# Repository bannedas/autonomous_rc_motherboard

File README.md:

# Autonomous RC motherboard

Remake of Benjamin Vedder made project https://github.com/vedderb/rise_sdvp

## Main

```
- Raspberry Compute module 3
	- HDMI
	- CAM0
	- ETHERNET
	- USB HOST (4 USB OUT)
	- microSD
- DAS board
- 2.4GHz radio by CC2520 
	- CC2592 extender
	- External antenna
- 420MHz - 470MHz radio by CC120
	- External antenna
-RTK-GNSS
	- UBLOX NEO M8P module
	- External antenna

- 40V to 12V 3A power
- 12V to 5V 1A power
- 12V to 3V3 2A power
- 3V3 to 1V8 500mA power

- 2x CAN output
- 4x PWM output
- 1 uart output

- Status LED for everything

```

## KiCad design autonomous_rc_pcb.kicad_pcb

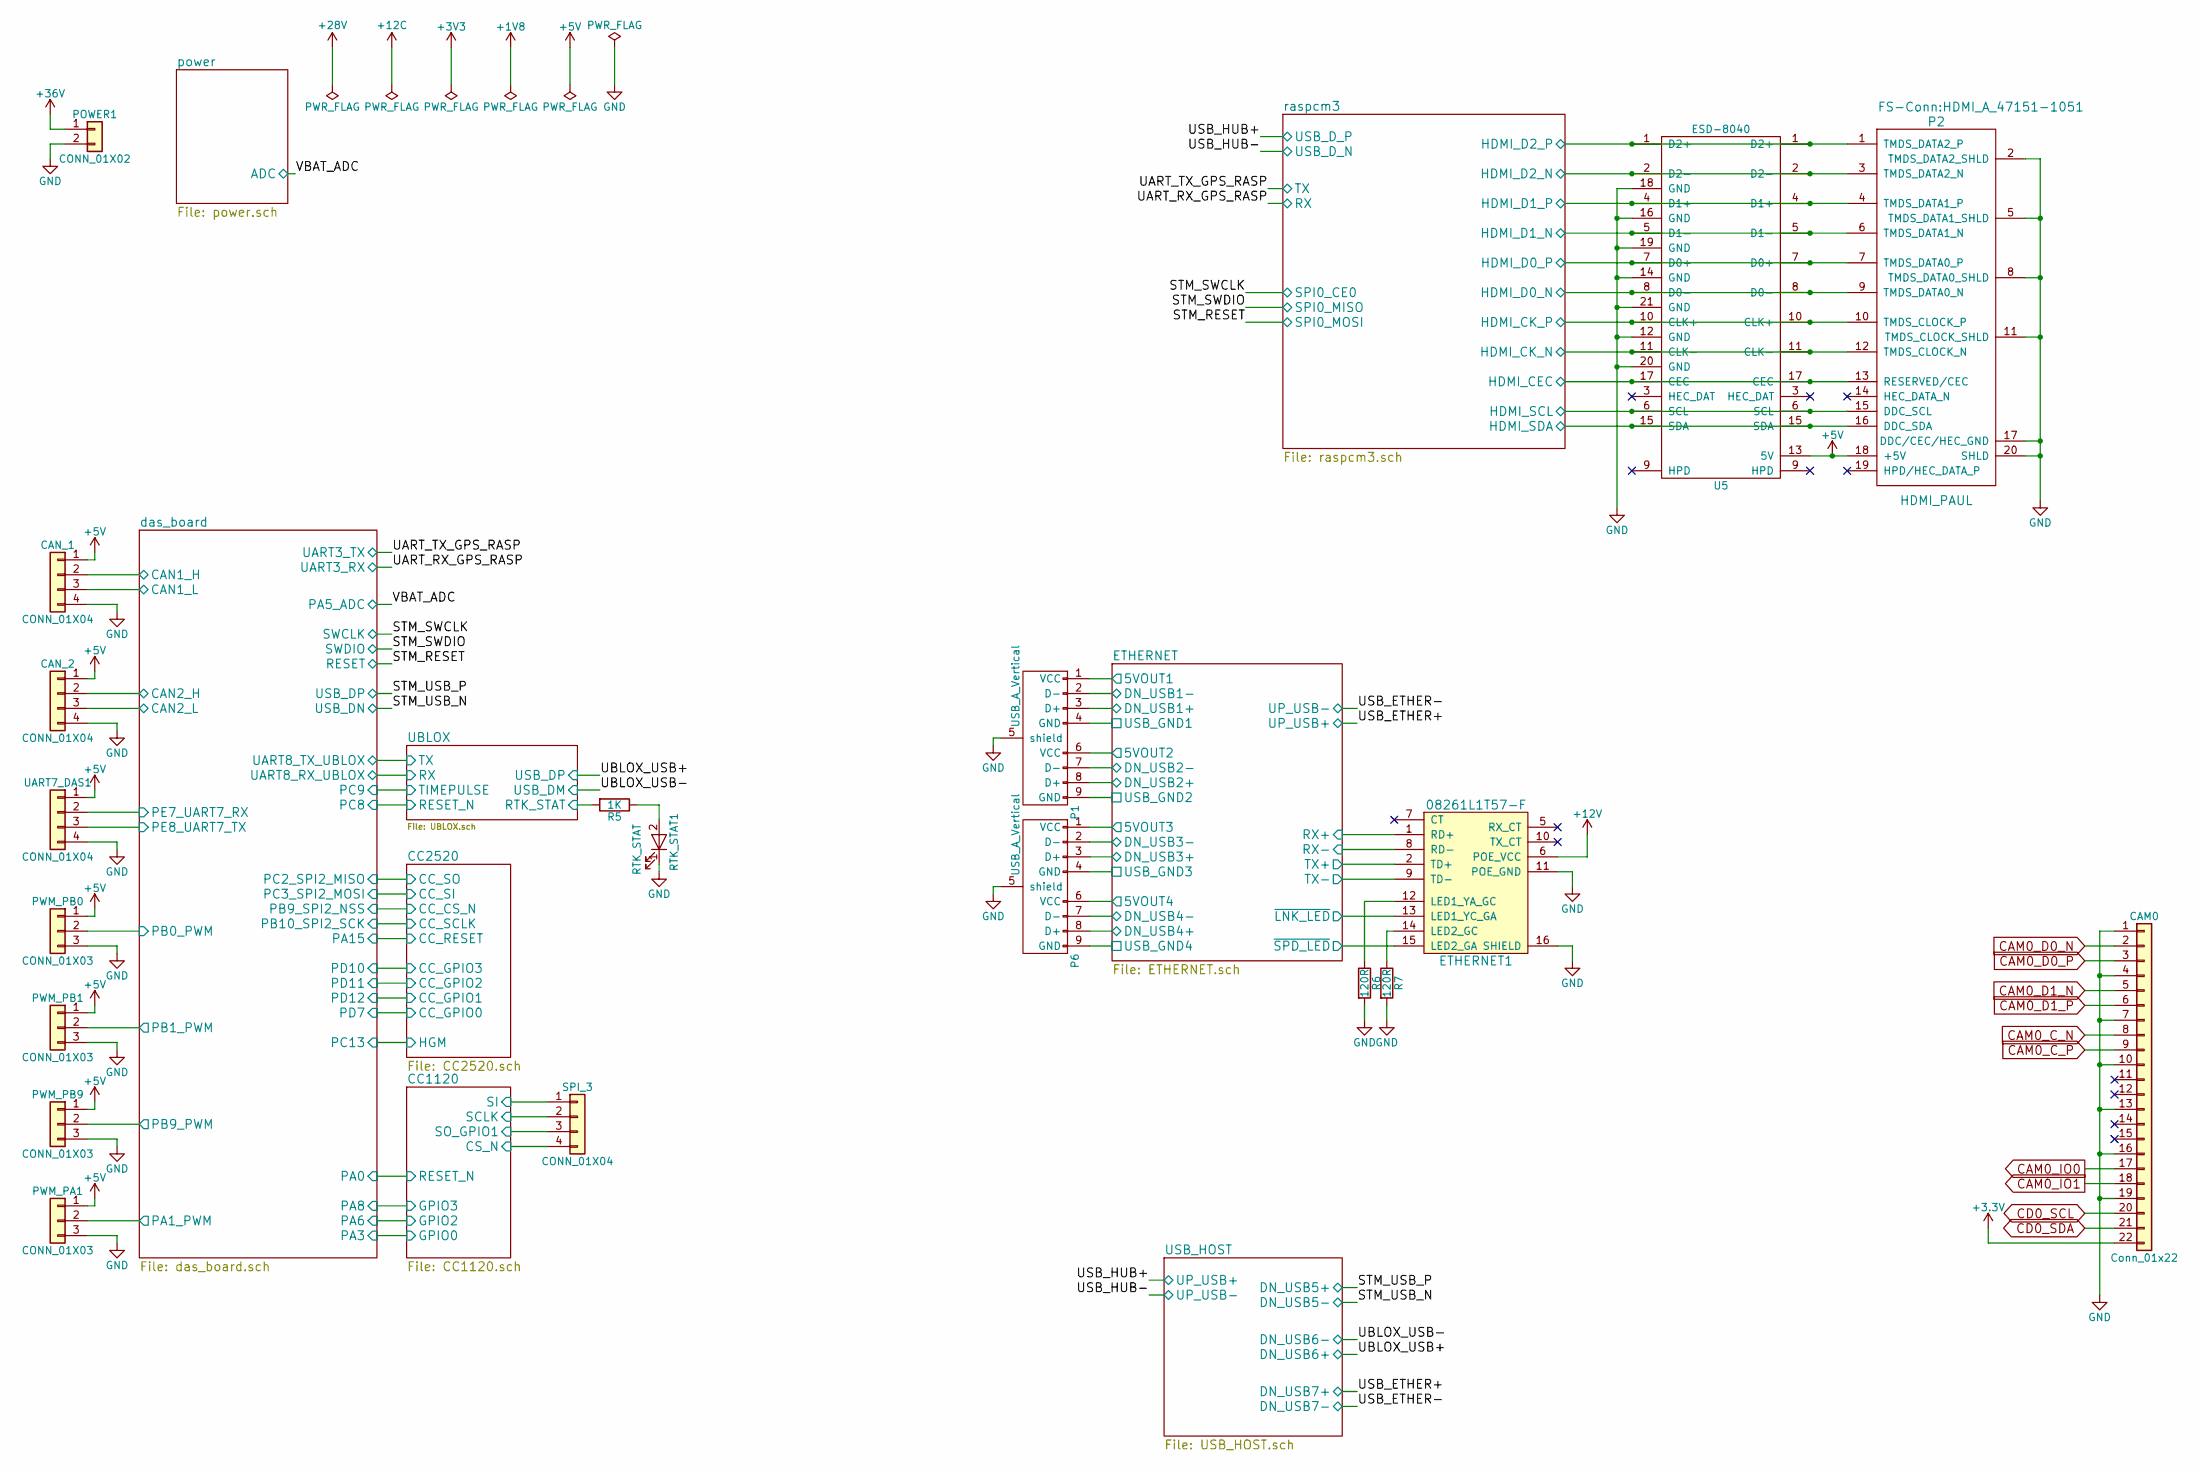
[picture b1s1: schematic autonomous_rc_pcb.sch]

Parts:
CAM0: Conn_01x22; 54548-2271; MPN 54548-2271
CAN_1, CAN_2: CONN_01X04; Molex_PicoBlade_53261-0471_04x1.25mm_Angled
ETHERNET1: 08261L1T57-F; 0826-1L1T-57-F; MPN 08261L1T57-F
P1, P6: USB_A_Vertical; USB-A-vertical
P2: HDMI_PAUL; HDMI_A_47151-1051
POWER1: CONN_01X02; DuraClik2
PWM_PA1: CONN_01X03; Molex_PicoBlade_53261-0371_03x1.25mm_Angled
PWM_PB0, PWM_PB1, PWM_PB9: CONN_01X03; Molex_PicoBlade_53261-0371_03x1.25mm_Angled
R5: 1K; R_0402
R6, R7: 120R; R_0402
RTK_STAT1: RTK_STAT; LED_0603
SPI_3: CONN_01X04; Molex_PicoBlade_53398-0471_04x1.25mm_Straight
U5: ESD-8040; ESD8040
UART7_DAS1: CONN_01X04; Molex_PicoBlade_53261-0471_04x1.25mm_Angled

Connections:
+5V: CAN_1.1, CAN_2.1, P2.18 (+5V), PWM_PA1.1, PWM_PB0.1, PWM_PB1.1, PWM_PB9.1, U5.13 (5V), UART7_DAS1.1; also elsewhere on the board
+12V: ETHERNET1.6 (POE_VCC); also elsewhere on the board
+36V: POWER1.1; also elsewhere on the board
/CC1120/CS_N: SPI_3.4; also elsewhere on the board
/CC1120/SCLK: SPI_3.2; also elsewhere on the board
/CC1120/SI: SPI_3.1; also elsewhere on the board
/CC1120/SO_GPIO1: SPI_3.3; also elsewhere on the board
/ETHERNET/5VOUT3: P1.1 (VCC); also elsewhere on the board
/ETHERNET/5VOUT4: P1.6 (VCC); also elsewhere on the board
/ETHERNET/DN_USB3+: P1.3 (D+); also elsewhere on the board
/ETHERNET/DN_USB3-: P1.2 (D-); also elsewhere on the board
/ETHERNET/DN_USB4+: P1.8 (D+); also elsewhere on the board
/ETHERNET/DN_USB4-: P1.7 (D-); also elsewhere on the board
/ETHERNET/RX+: ETHERNET1.1 (RD+); also elsewhere on the board
/ETHERNET/RX-: ETHERNET1.8 (RD-); also elsewhere on the board
/ETHERNET/TX+: ETHERNET1.2 (TD+); also elsewhere on the board
/ETHERNET/TX-: ETHERNET1.9 (TD-); also elsewhere on the board
/ETHERNET/USB_GND3: P1.4 (GND); also elsewhere on the board
/ETHERNET/USB_GND4: P1.9 (GND); also elsewhere on the board
/ETHERNET/~LNK_LED: ETHERNET1.13 (LED1_YC_GA); also elsewhere on the board
/ETHERNET/~SPD_LED: ETHERNET1.15 (LED2_GA); also elsewhere on the board
/UBLOX/RTK_STAT: R5.2; also elsewhere on the board
/das_board/CAN1_H: CAN_1.2; also elsewhere on the board
/das_board/CAN1_L: CAN_1.3; also elsewhere on the board
/das_board/CAN2_H: CAN_2.2; also elsewhere on the board
/das_board/CAN2_L: CAN_2.3; also elsewhere on the board
/das_board/PA1_PWM: PWM_PA1.2; also elsewhere on the board
/das_board/PB0_PWM: PWM_PB0.2; also elsewhere on the board
/das_board/PB1_PWM: PWM_PB1.2; also elsewhere on the board
/das_board/PB9_PWM: PWM_PB9.2; also elsewhere on the board
/das_board/PE7_UART7_RX: UART7_DAS1.2; also elsewhere on the board
/das_board/PE8_UART7_TX: UART7_DAS1.3; also elsewhere on the board
/raspcm3/HDMI_CEC: P2.13 (RESERVED/CEC), U5.17 (CEC); also elsewhere on the board
/raspcm3/HDMI_CK_N: P2.12 (TMDS_CLOCK_N), U5.11 (CLK-); also elsewhere on the board
/raspcm3/HDMI_CK_P: P2.10 (TMDS_CLOCK_P), U5.10 (CLK+); also elsewhere on the board
/raspcm3/HDMI_D0_N: P2.9 (TMDS_DATA0_N), U5.8 (D0-); also elsewhere on the board
/raspcm3/HDMI_D0_P: P2.7 (TMDS_DATA0_P), U5.7 (D0+); also elsewhere on the board
/raspcm3/HDMI_D1_N: P2.6 (TMDS_DATA1_N), U5.5 (D1-); also elsewhere on the board
/raspcm3/HDMI_D1_P: P2.4 (TMDS_DATA1_P), U5.4 (D1+); also elsewhere on the board
/raspcm3/HDMI_D2_N: P2.3 (TMDS_DATA2_N), U5.2 (D2-); also elsewhere on the board
/raspcm3/HDMI_D2_P: P2.1 (TMDS_DATA2_P), U5.1 (D2+); also elsewhere on the board
/raspcm3/HDMI_SCL: P2.15 (DDC_SCL), U5.6 (SCL); also elsewhere on the board
/raspcm3/HDMI_SDA: P2.16 (DDC_SDA), U5.15 (SDA); also elsewhere on the board
CAM0_C_N: CAM0.8; also elsewhere on the board
CAM0_C_P: CAM0.9; also elsewhere on the board
CAM0_D0_N: CAM0.2; also elsewhere on the board
CAM0_D0_P: CAM0.3; also elsewhere on the board
CAM0_D1_N: CAM0.5; also elsewhere on the board
CAM0_D1_P: CAM0.6; also elsewhere on the board
CAM0_IO0: CAM0.17; also elsewhere on the board
CAM0_IO1: CAM0.18; also elsewhere on the board
CD0_SCL: CAM0.20; also elsewhere on the board
CD0_SDA: CAM0.21; also elsewhere on the board
GND: CAM0.1, CAM0.4, CAM0.7, CAM0.10, CAM0.13, CAM0.16, CAM0.19, CAN_1.4, CAN_2.4, ETHERNET1.11 (POE_GND), ETHERNET1.16 (SHIELD), P1.5 (shield), P2.2 (TMDS_DATA2_SHLD), P2.5 (TMDS_DATA1_SHLD), P2.8 (TMDS_DATA0_SHLD), P2.11 (TMDS_CLOCK_SHLD), P2.17 (DDC/CEC/HEC_GND), P2.20 (SHLD), P6.5 (shield), POWER1.2, PWM_PA1.3, PWM_PB0.3, PWM_PB1.3, PWM_PB9.3, R6.2, R7.2, RTK_STAT1.1 (K), U5.12 (GND), U5.14 (GND), U5.16 (GND), U5.18 (GND), U5.19 (GND), U5.20 (GND), U5.21 (GND), UART7_DAS1.4; also elsewhere on the board
unnamed 253: R5.1, RTK_STAT1.2 (A); also elsewhere on the board
unnamed: ETHERNET1.12 (LED1_YA_GC), R6.1
unnamed: ETHERNET1.14 (LED2_GC), R7.1

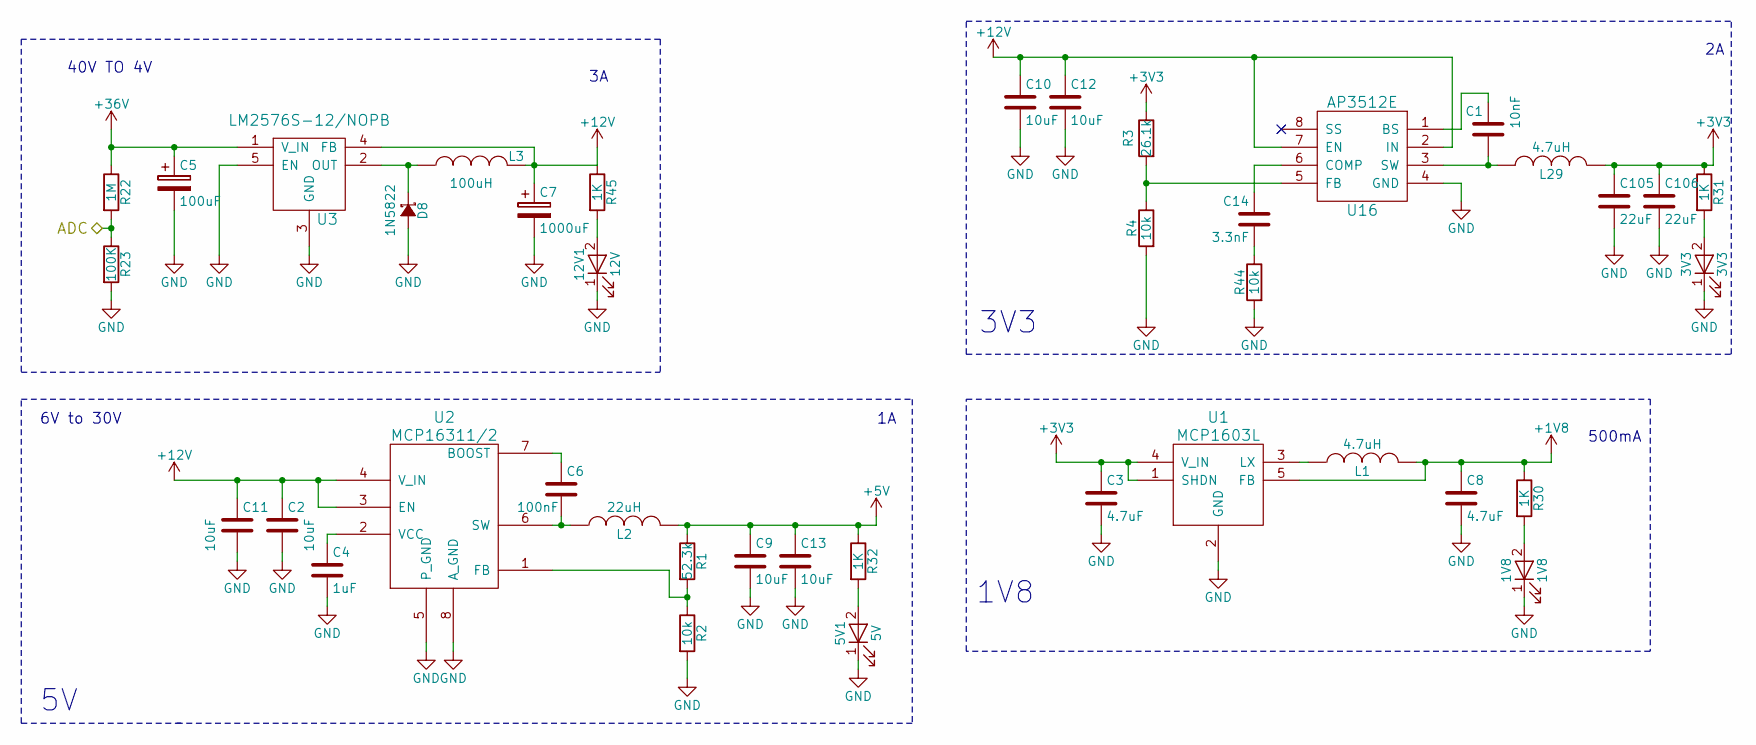
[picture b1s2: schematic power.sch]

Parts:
1V8: 1V8; LED_0603
3V3: 3V3; LED_0603
5V1: 5V; LED_0603
12V1: 12V; LED_0603
C1: 10nF; C_0402
C2, C9, C11, C13: 10uF; C_0402
C3, C8: 4.7uF; C_0402
C4: 1uF; C_0402
C5: 100uF; CP_Radial_D8.0mm_P3.50mm
C6: 100nF; C_0402
C7: 1000uF; CP_Radial_D8.0mm_P5.00mm; MPN EEUFR1C102LB
C10, C12: 10uF; C_0805_HandSoldering
C14: 3.3nF; C_0402
C105, C106: 22uF; C_0805_HandSoldering
D8: 1N5822; D_DO-201AD_P5.08mm_Vertical_AnodeUp
L1: 4.7uH; R_0805_HandSoldering; MPN CPI0805E4R7R-10
L2: 22uH; L_Coilcraft_XAL5030; MPN VLCF5020T-220MR75-1
L3: 100uH; L_Vishay_IHLP-4040; MPN MSS1210-104KED
L29: 4.7uH; L_Taiyo-Yuden_NR-50xx_HandSoldering; MPN SRN4018-4R7M
R1: 52.3k; R_0402
R2: 10k; R_0402
R3: 26.1k; R_0402_1005Metric
R4, R44: 10k; R_0402_1005Metric
R22: 1M; R_0402
R23: 100K; R_0402
R30, R31, R32, R45: 1K; R_0402
U1: MCP1603L; TSOT-23-5; MPN MCP1603LT-180I/OS
U2: MCP16311/2; MSOP-8-1EP_3x3mm_Pitch0.65mm
U3: LM2576S-12/NOPB; TO-263-5_TabPin3; MPN LM2576S-12/NOPB
U16: AP3512E; PowerIntegrations_SO-8

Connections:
+1V8: C8.1, L1.2, R30.1, U1.5 (FB); also elsewhere on the board
+5V: C9.1, C13.1, L2.2, R1.1, R32.1; also elsewhere on the board
+12V: C2.1, C7.1, C10.1, C11.1, C12.1, L3.2, R45.1, U2.3 (EN), U2.4 (V_IN), U3.4 (FB), U16.2 (IN), U16.7 (EN); also elsewhere on the board
+36V: C5.1, R22.1, U3.1 (V_IN); also elsewhere on the board
/VBAT_ADC: R22.2, R23.1; also elsewhere on the board
GND: 1V8.1 (K), 3V3.1 (K), 5V1.1 (K), 12V1.1 (K), C2.2, C3.2, C4.2, C5.2, C7.2, C8.2, C9.2, C10.2, C11.2, C12.2, C13.2, C105.2, C106.2, D8.A, R2.2, R4.2, R23.2, R44.2, U1.2 (GND), U2.5 (P_GND), U2.8 (A_GND), U3.3 (GND), U3.5 (EN), U16.4 (GND); also elsewhere on the board
unnamed: 12V1.2 (A), R45.2
unnamed: C1.1, U16.1 (BS)
unnamed: C1.2, L29.2, U16.3 (SW)
unnamed: C4.1, U2.2 (VCC)
unnamed: C6.1, U2.7 (BOOST)
unnamed: C6.2, L2.1, U2.6 (SW)
unnamed: C14.1, U16.6 (COMP)
unnamed: C14.2, R44.1
unnamed: 1V8.2 (A), R30.2
unnamed: 3V3.2 (A), R31.2
unnamed 259: 5V1.2 (A), R32.2; also elsewhere on the board
unnamed: D8.K, L3.1, U3.2 (OUT)
unnamed: L1.1, U1.3 (LX)
unnamed: R1.2, R2.1, U2.1 (FB)
unnamed: R3.2, R4.1, U16.5 (FB)

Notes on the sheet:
6V to 30V
1V8
3V3
500mA
40V TO 4V

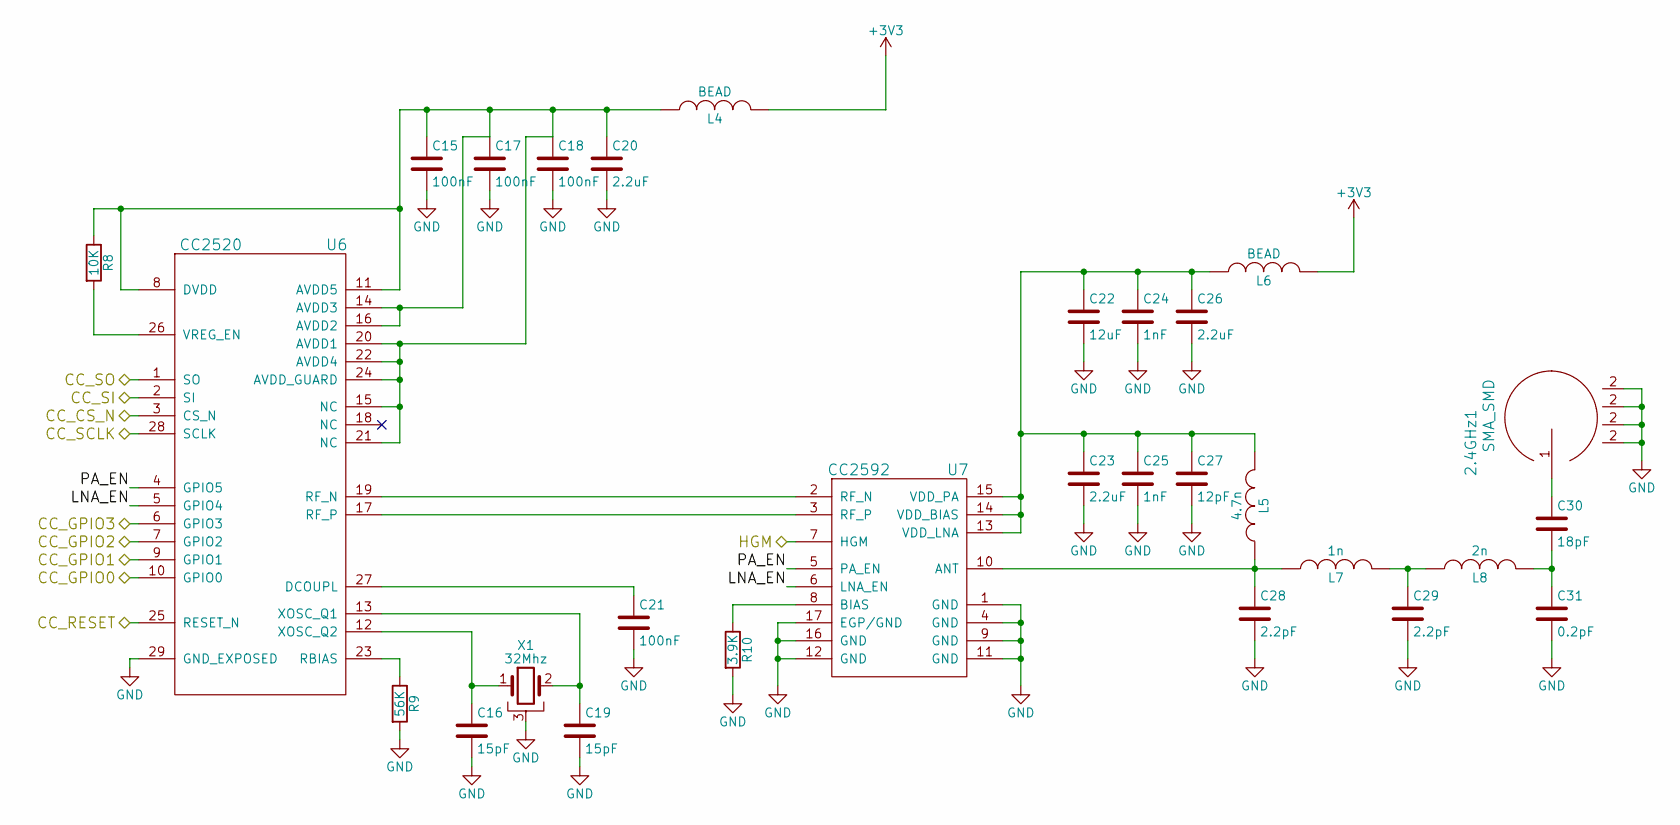
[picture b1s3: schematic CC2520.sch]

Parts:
2.4GHz1: SMA_SMD; SMA_THT_Jack_Straight
C15, C17, C18, C21: 100nF; C_0402
C16, C19: 15pF; C_0603
C20, C23, C26: 2.2uF; C_0603_1608Metric
C22: 12uF; C_1210_3225Metric
C24, C25: 1nF; C_0402
C27: 12pF; C_1210_3225Metric
C28, C29: 2.2pF; C_0603_1608Metric
C30: 18pF; C_0402
C31: 0.2pF; C_0402
L4, L6: BEAD; R_0603; MPN BLM18HE152SN1
L5: 4.7n; R_0402
L7: 1n; R_0402
L8: 2n; R_0402
R8: 10K; R_0402
R9: 56K; R_0402
R10: 3.9K; R_0402
U6: CC2520; QFN-28-1EP_5x5mm_Pitch0.5mm; MPN CC2520RHDR
U7: CC2592; QFN-16-1EP_4x4mm_Pitch0.65mm; MPN CC2592RGVR
X1: 32Mhz; Crystal_SMD_5032-4pin_5.0x3.2mm

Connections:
/CC2520/CC_CS_N: U6.3 (CS_N); also elsewhere on the board
/CC2520/CC_GPIO0: U6.10 (GPIO0); also elsewhere on the board
/CC2520/CC_GPIO1: U6.9 (GPIO1); also elsewhere on the board
/CC2520/CC_GPIO2: U6.7 (GPIO2); also elsewhere on the board
/CC2520/CC_GPIO3: U6.6 (GPIO3); also elsewhere on the board
/CC2520/CC_RESET: U6.25 (RESET_N); also elsewhere on the board
/CC2520/CC_SCLK: U6.28 (SCLK); also elsewhere on the board
/CC2520/CC_SI: U6.2 (SI); also elsewhere on the board
/CC2520/CC_SO: U6.1 (SO); also elsewhere on the board
/CC2520/HGM: U7.7 (HGM); also elsewhere on the board
/CC2520/LNA_EN: U6.5 (GPIO4), U7.6 (LNA_EN)
/CC2520/PA_EN: U6.4 (GPIO5), U7.5 (PA_EN)
GND: 2.4GHz1.2, C15.2, C16.2, C17.2, C18.2, C19.2, C20.2, C21.2, C22.2, C23.2, C24.2, C25.2, C26.2, C27.2, C28.2, C29.2, C31.2, R9.2, R10.2, U6.29 (GND_EXPOSED), U7.1 (GND), U7.4 (GND), U7.9 (GND), U7.11 (GND), U7.12 (GND), U7.16 (GND), U7.17 (EGP/GND), X1.3; also elsewhere on the board
unnamed: C15.1, C17.1, C18.1, C20.1, L4.1, R8.1, U6.8 (DVDD), U6.11 (AVDD5), U6.14 (AVDD3), U6.15 (NC), U6.16 (AVDD2), U6.20 (AVDD1), U6.21 (NC), U6.22 (AVDD4), U6.24 (AVDD_GUARD)
unnamed: C16.1, U6.12 (XOSC_Q2), X1.1
unnamed: C19.1, U6.13 (XOSC_Q1), X1.2
unnamed: C21.1, U6.27 (DCOUPL)
unnamed: C22.1, C23.1, C24.1, C25.1, C26.1, C27.1, L5.2, L6.1, U7.13 (VDD_LNA), U7.14 (VDD_BIAS), U7.15 (VDD_PA)
unnamed 216: C28.1, L5.1, L7.1, U7.10 (ANT); also elsewhere on the board
unnamed: C29.1, L7.2, L8.1
unnamed 218: 2.4GHz1.1, C30.1; also elsewhere on the board
unnamed: C30.2, C31.1, L8.2
unnamed: R8.2, U6.26 (VREG_EN)
unnamed: R9.1, U6.23 (RBIAS)
unnamed: R10.1, U7.8 (BIAS)
unnamed: U6.17 (RF_P), U7.3 (RF_P)
unnamed: U6.19 (RF_N), U7.2 (RF_N)

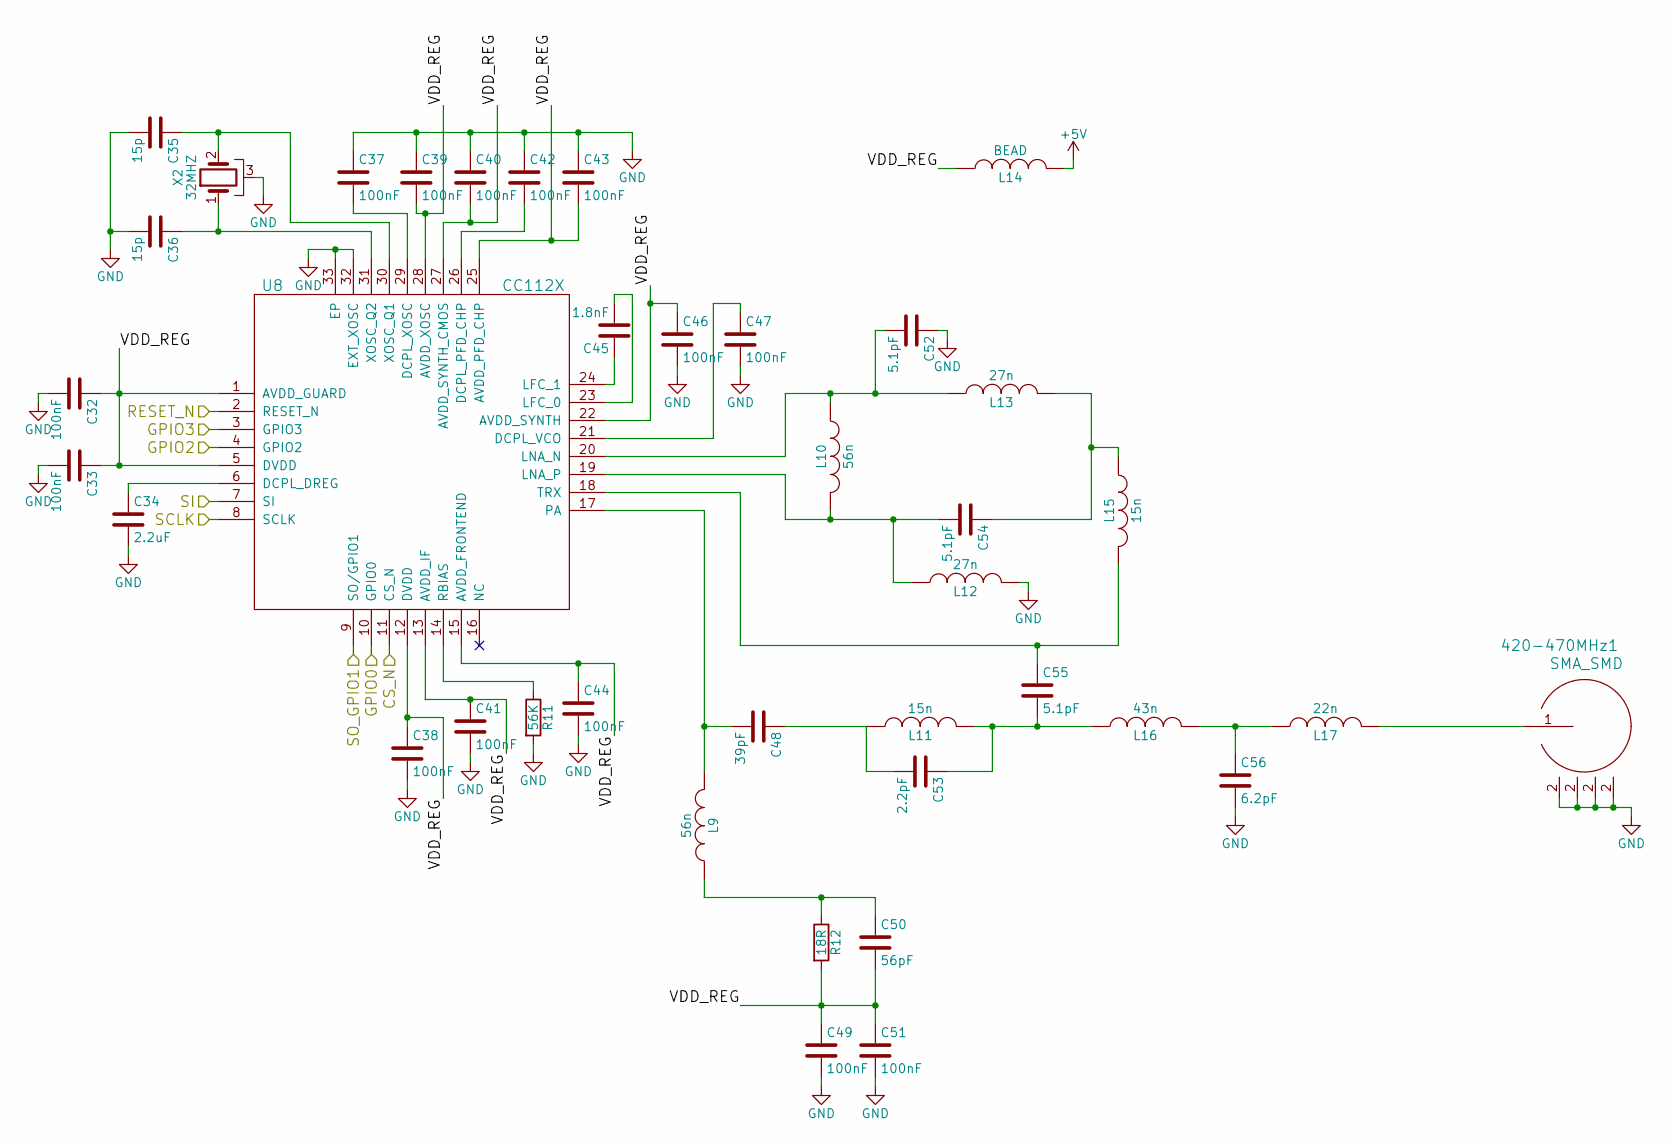
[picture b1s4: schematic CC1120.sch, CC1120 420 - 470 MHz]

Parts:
420-470MHz1: SMA_SMD; SMA_THT_Jack_Straight
C32, C33, C37, C38, C39, C40, C41, C42, C43, C44, C46, C47, C49, C51: 100nF; C_0402
C34: 2.2uF; C_0603
C35, C36: 15p; C_0603
C45: 1.8nF; C_0402
C48: 39pF; C_0402
C50: 56pF; C_0402
C52, C54, C55: 5.1pF; C_0402
C53: 2.2pF; C_0402
C56: 6.2pF; C_0402
L9, L10: 56n; R_0402
L11, L15: 15n; R_0402
L12, L13: 27n; R_0402
L14: BEAD; R_0603; MPN BLM18HE152SN1
L16: 43n; R_0402
L17: 22n; R_0402
R11: 56K; R_0402
R12: 18R; R_0402
U8: CC112X; QFN-32-1EP_5x5mm_Pitch0.5mm
X2: 32MHZ; Crystal_SMD_5032-4pin_5.0x3.2mm

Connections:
+5V: L14.2; also elsewhere on the board
/CC1120/CS_N: U8.11 (CS_N); also elsewhere on the board
/CC1120/GPIO0: U8.10 (GPIO0); also elsewhere on the board
/CC1120/GPIO2: U8.4 (GPIO2); also elsewhere on the board
/CC1120/GPIO3: U8.3 (GPIO3); also elsewhere on the board
/CC1120/SCLK: U8.8 (SCLK); also elsewhere on the board
/CC1120/SI: U8.7 (SI); also elsewhere on the board
/CC1120/SO_GPIO1: U8.9 (SO/GPIO1); also elsewhere on the board
/CC1120/VDD_REG: C32.1, C33.1, C38.1, C39.2, C40.2, C41.1, C43.2, C44.1, C46.1, C49.1, C50.2, C51.1, L14.1, R12.2, U8.1 (AVDD_GUARD), U8.5 (DVDD), U8.12 (DVDD), U8.13 (AVDD_IF), U8.15 (AVDD_FRONTEND), U8.22 (AVDD_SYNTH), U8.25 (AVDD_PFD_CHP), U8.27 (AVDD_SYNTH_CMOS), U8.28 (AVDD_XOSC)
/das_board/PA0: U8.2 (RESET_N); also elsewhere on the board
GND: 420-470MHz1.2, C32.2, C33.2, C34.2, C35.2, C36.2, C37.1, C38.2, C39.1, C40.1, C41.2, C42.1, C43.1, C44.2, C46.2, C47.2, C49.2, C51.2, C52.1, C56.2, L12.2, R11.2, U8.32 (EXT_XOSC), U8.33 (EP), X2.3; also elsewhere on the board
unnamed: C34.1, U8.6 (DCPL_DREG)
unnamed: C35.1, U8.30 (XOSC_Q1), X2.2
unnamed: C36.1, U8.31 (XOSC_Q2), X2.1
unnamed: C37.2, U8.29 (DCPL_XOSC)
unnamed: C42.2, U8.26 (DCPL_PFD_CHP)
unnamed: C45.1, U8.24 (LFC_1)
unnamed: C45.2, U8.23 (LFC_0)
unnamed: C47.1, U8.21 (DCPL_VCO)
unnamed: C48.1, C53.2, L11.1
unnamed 229: C48.2, L9.2, U8.17 (PA); also elsewhere on the board
unnamed: C50.1, L9.1, R12.1
unnamed: C52.2, L10.1, L13.1, U8.20 (LNA_N)
unnamed: C53.1, C55.2, L11.2, L16.1
unnamed: C54.1, L13.2, L15.1
unnamed: C54.2, L10.2, L12.1, U8.19 (LNA_P)
unnamed: C55.1, L15.2, U8.18 (TRX)
unnamed: C56.1, L16.2, L17.1
unnamed 273: 420-470MHz1.1, L17.2; also elsewhere on the board
unnamed: R11.1, U8.14 (RBIAS)

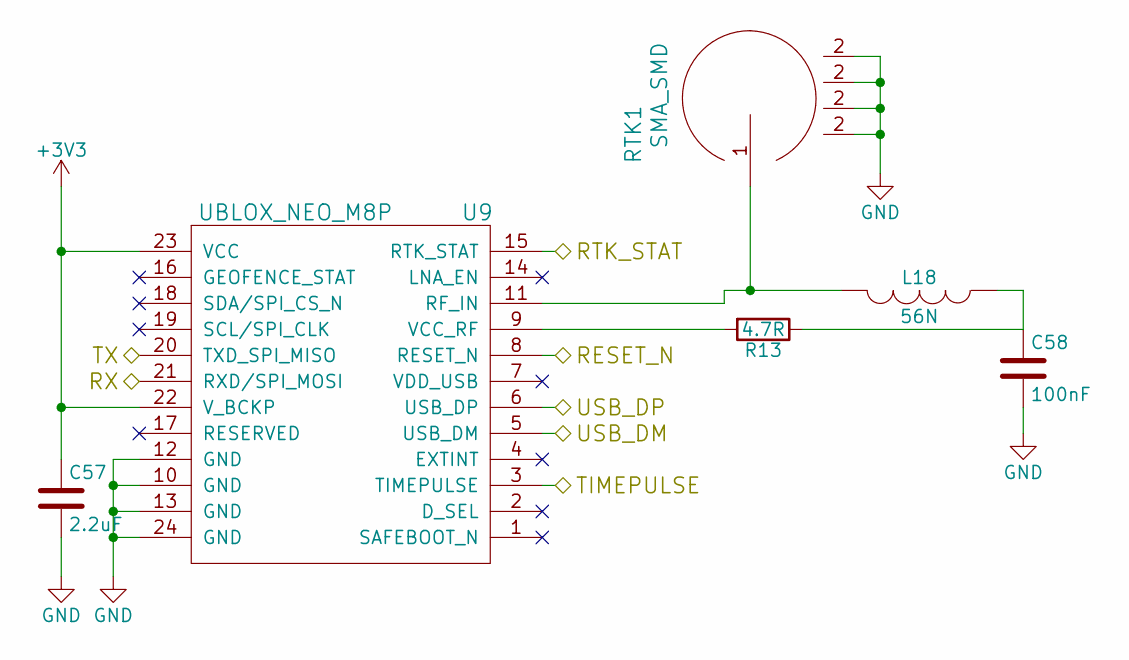
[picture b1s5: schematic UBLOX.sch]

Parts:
C57: 2.2uF; C_0603
C58: 100nF; C_0402
L18: 56N; R_0402
R13: 4.7R; R_0402
RTK1: SMA_SMD; SMA_THT_Jack_Straight
U9: UBLOX_NEO_M8P; U-BLOX-NEO-M8P

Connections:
GND: C57.2, C58.2, RTK1.2, U9.10 (GND), U9.12 (GND), U9.13 (GND), U9.24 (GND); also elsewhere on the board
unnamed: C58.1, L18.1, R13.1
unnamed 274: L18.2, RTK1.1, U9.11 (RF_IN); also elsewhere on the board
unnamed 283: R13.2, U9.9 (VCC_RF); also elsewhere on the board

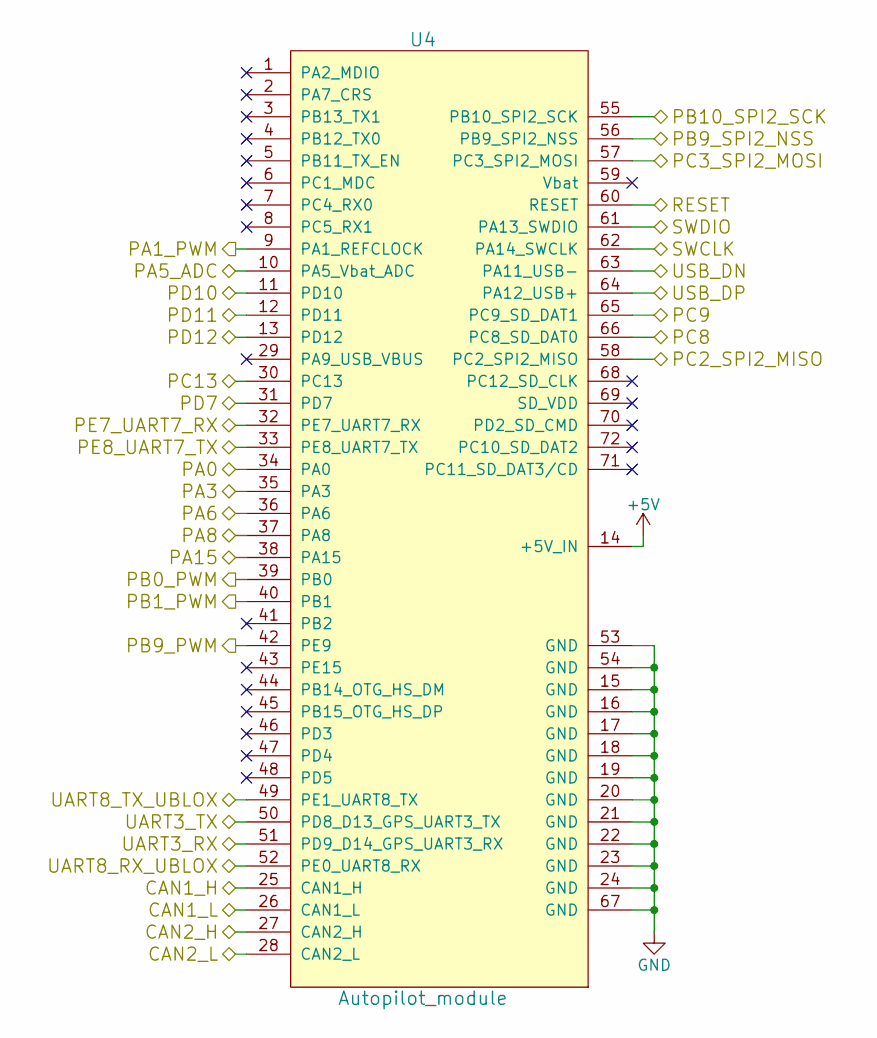
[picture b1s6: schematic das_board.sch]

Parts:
U4: Autopilot_module; Autopilot

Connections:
+5V: U4.14 (+5V_IN); also elsewhere on the board
/CC1120/GPIO0: U4.35 (PA3); also elsewhere on the board
/CC1120/GPIO2: U4.36 (PA6); also elsewhere on the board
/CC1120/GPIO3: U4.37 (PA8); also elsewhere on the board
/CC2520/CC_CS_N: U4.56 (PB9_SPI2_NSS); also elsewhere on the board
/CC2520/CC_GPIO0: U4.31 (PD7); also elsewhere on the board
/CC2520/CC_GPIO1: U4.13 (PD12); also elsewhere on the board
/CC2520/CC_GPIO2: U4.12 (PD11); also elsewhere on the board
/CC2520/CC_GPIO3: U4.11 (PD10); also elsewhere on the board
/CC2520/CC_RESET: U4.38 (PA15); also elsewhere on the board
/CC2520/CC_SCLK: U4.55 (PB10_SPI2_SCK); also elsewhere on the board
/CC2520/CC_SI: U4.57 (PC3_SPI2_MOSI); also elsewhere on the board
/CC2520/CC_SO: U4.58 (PC2_SPI2_MISO); also elsewhere on the board
/CC2520/HGM: U4.30 (PC13); also elsewhere on the board
/STM_RESET: U4.60 (RESET); also elsewhere on the board
/STM_SWCLK: U4.62 (PA14_SWCLK); also elsewhere on the board
/STM_SWDIO: U4.61 (PA13_SWDIO); also elsewhere on the board
/STM_USB_N: U4.63 (PA11_USB-); also elsewhere on the board
/STM_USB_P: U4.64 (PA12_USB+); also elsewhere on the board
/UART_RX_GPS_RASP: U4.51 (PD9_D14_GPS_UART3_RX); also elsewhere on the board
/UART_TX_GPS_RASP: U4.50 (PD8_D13_GPS_UART3_TX); also elsewhere on the board
/UBLOX/RX: U4.52 (PE0_UART8_RX); also elsewhere on the board
/UBLOX/TX: U4.49 (PE1_UART8_TX); also elsewhere on the board
/VBAT_ADC: U4.10 (PA5_Vbat_ADC); also elsewhere on the board
/das_board/CAN1_H: U4.25 (CAN1_H); also elsewhere on the board
/das_board/CAN1_L: U4.26 (CAN1_L); also elsewhere on the board
/das_board/CAN2_H: U4.27 (CAN2_H); also elsewhere on the board
/das_board/CAN2_L: U4.28 (CAN2_L); also elsewhere on the board
/das_board/PA0: U4.34 (PA0); also elsewhere on the board
/das_board/PA1_PWM: U4.9 (PA1_REFCLOCK); also elsewhere on the board
/das_board/PB0_PWM: U4.39 (PB0); also elsewhere on the board
/das_board/PB1_PWM: U4.40 (PB1); also elsewhere on the board
/das_board/PB9_PWM: U4.42 (PE9); also elsewhere on the board
/das_board/PC8: U4.66 (PC8_SD_DAT0); also elsewhere on the board
/das_board/PC9: U4.65 (PC9_SD_DAT1); also elsewhere on the board
/das_board/PE7_UART7_RX: U4.32 (PE7_UART7_RX); also elsewhere on the board
/das_board/PE8_UART7_TX: U4.33 (PE8_UART7_TX); also elsewhere on the board
GND: U4.15 (GND), U4.16 (GND), U4.17 (GND), U4.18 (GND), U4.19 (GND), U4.20 (GND), U4.21 (GND), U4.22 (GND), U4.23 (GND), U4.24 (GND), U4.53 (GND), U4.54 (GND), U4.67 (GND); also elsewhere on the board
